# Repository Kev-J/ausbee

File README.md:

Overview
============

Architecture Using STM32 By Eirbot ENSEIRB-MATMECA.
This tool is provided for building automatically a complete STM32F project.

Licence
=============

See LICENCE file.

Usage
=============

- git clone the repository or download the snapshot of the last version.
- If you choose the git clone method, it is recommended to use a tagged version (git checkout vX.X).
- Configure your board (type "make help" for further informations).
- write your source code in Project/src (headers and source files).
- run "make"
- run "make program" for downloading your code into your device.

For further informations, please visit our wiki : https://github.com/Kev-J/ausbee/wiki

Features
=============

- FreeRTOS
- ST Std_Periph_Driver
- libausbee
- stm32flash

Dependencies
=============
* gperf
* flex
* bison
* libncurses-dev (for menuconfig)
* wget
* unzip
* tar
* stm32flash

Please note that this project is using many third party programs. Please ensure
that your setup have all the requirements before using them. For instance,
have a look to the [GCC arm embedded README](https://launchpadlibrarian.net/209775724/readme.txt)
and check that you have all the dependencies installed on your machine before
trying to compile anything.

Authors of the project
=============

Please see AUTHORS

Bugs, patch, requests
=============

https://github.com/Kev-J/ausbee
or
<ausbee@googlegroups.com>

Maintainer : Kevin JOLY <joly.kevin25@gmail.com>

Related to this project
=============

libausbee
-------------
https://github.com/Kev-J/libausbee

ausbee-hardware
-------------
https://github.com/Kev-J/ausbee-hardware

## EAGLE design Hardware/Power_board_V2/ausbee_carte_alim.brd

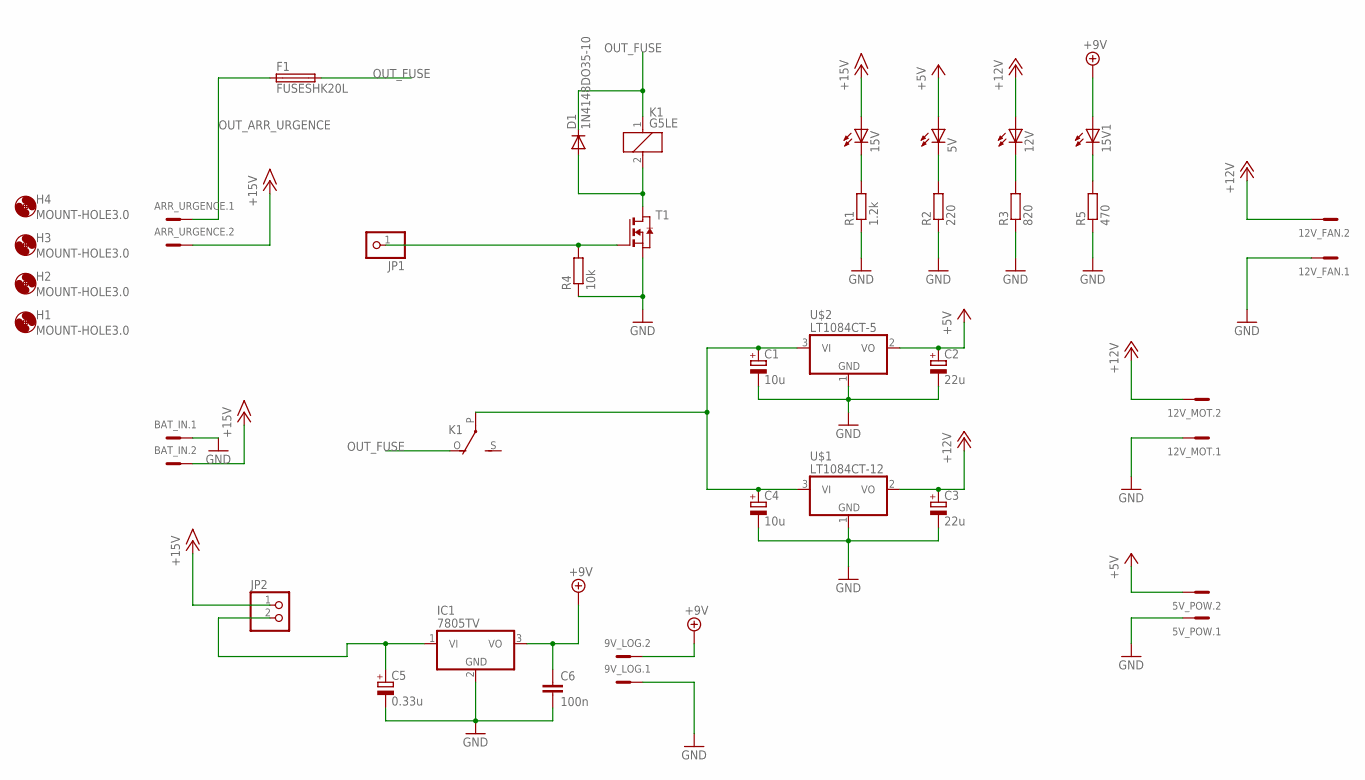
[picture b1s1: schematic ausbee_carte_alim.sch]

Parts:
5V, 12V, 15V, 15V1: LED3MM
5V_POW, 9V_LOG, 12V_FAN, 12V_MOT: MCV2
ARR_URGENCE: MCV2
BAT_IN: MCV2
C1, C4: 10u; E5-8,5
C2, C3: 22u; CT7343
C5: 0.33u; E2,5-5
C6: 100n; C0805
D1: 1N4148DO35-10; DO35-10
F1: FUSESHK20L; SHK20L
H1, H2, H3, H4: MOUNT-HOLE3.0; 3,0
IC1: 7805TV; TO220V
JP1: PINHD-1X1; 1X01
JP2: PINHD-1X2; 1X02
K1: G5LE
R1: 1.2k; 0309V
R2: 220; 0309V
R3: 820; 0309V
R4: 10k; 0309V
R5: 470; 0309V
T1: NMOSSOT23; SOT-23
U$1: LT1084CT-12; TO220V
U$2: LT1084CT-5; TO220V

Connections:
+5V: 5V.A, 5V_POW.2, C2.+, U$2.2 (VO)
+9V: 9V_LOG.2, 15V1.A, C6.1, IC1.3 (VO)
+12V: 12V.A, 12V_FAN.2, 12V_MOT.2, C3.+, U$1.2 (VO)
+15V: 15V.A, ARR_URGENCE.2, BAT_IN.2, JP2.1
GND: 5V_POW.1, 9V_LOG.1, 12V_FAN.1, 12V_MOT.1, BAT_IN.1, C1.-, C2.-, C3.-, C4.-, C5.-, C6.2, IC1.2 (GND), R1.1, R2.1, R3.1, R4.1, R5.1, T1.2 (S), U$1.1 (GND), U$2.1 (GND)
unnamed: 12V.K (C), R3.2
unnamed: 5V.K (C), R2.2
unnamed: 15V.K (C), R1.2
unnamed: C1.+, C4.+, K1.P, U$1.3 (VI), U$2.3 (VI)
unnamed: D1.A, K1.2, T1.1 (D)
unnamed: JP1.1, R4.2, T1.3 (G)
unnamed: C5.+, IC1.1 (VI), JP2.2
unnamed: 15V1.K (C), R5.2
OUT_ARR_URGENCE: ARR_URGENCE.1, F1.1A (1)
OUT_FUSE: D1.C, F1.2A (2), K1.1, K1.O

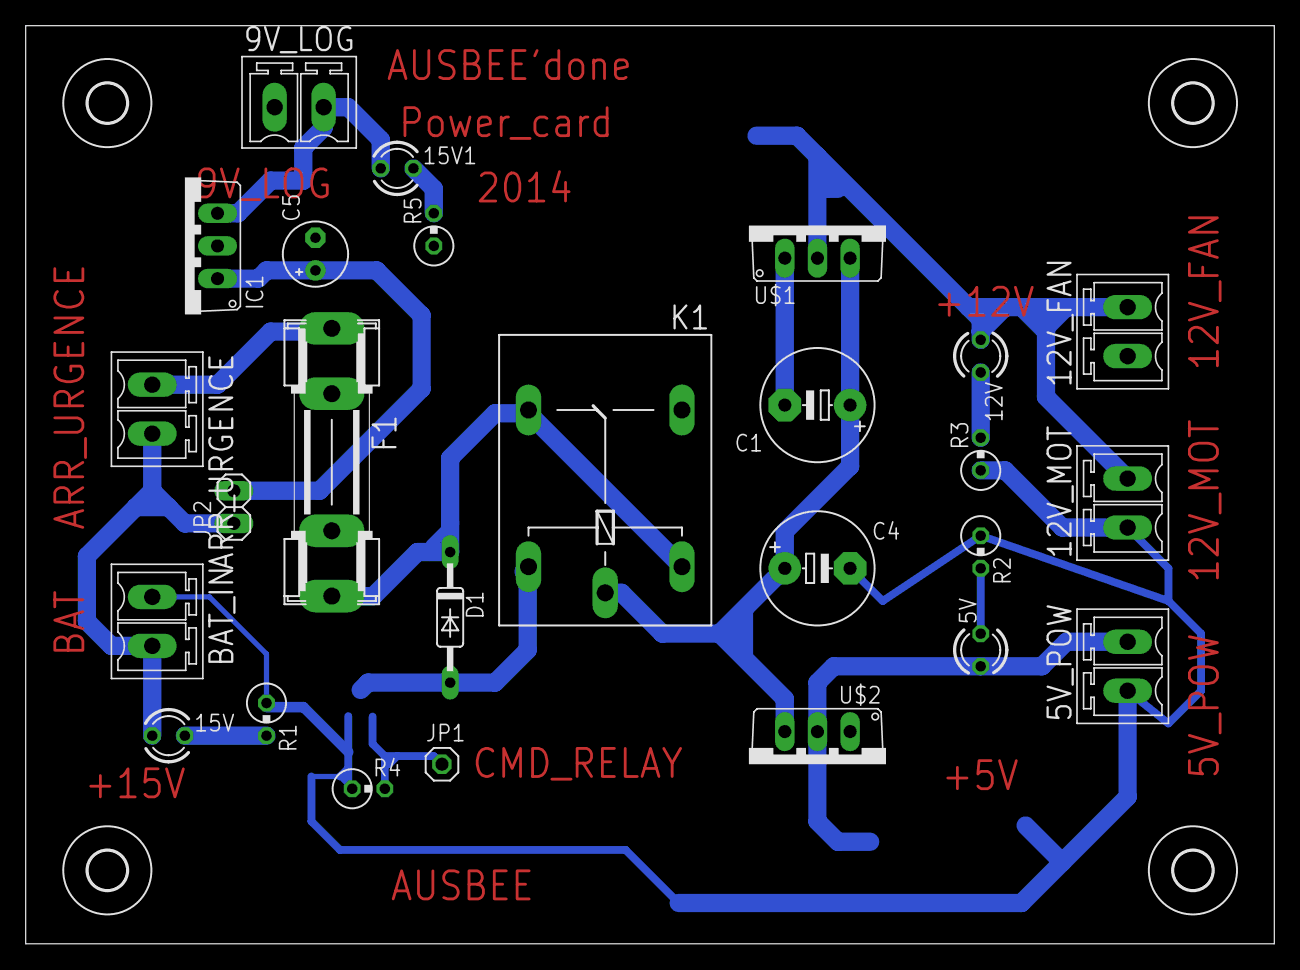
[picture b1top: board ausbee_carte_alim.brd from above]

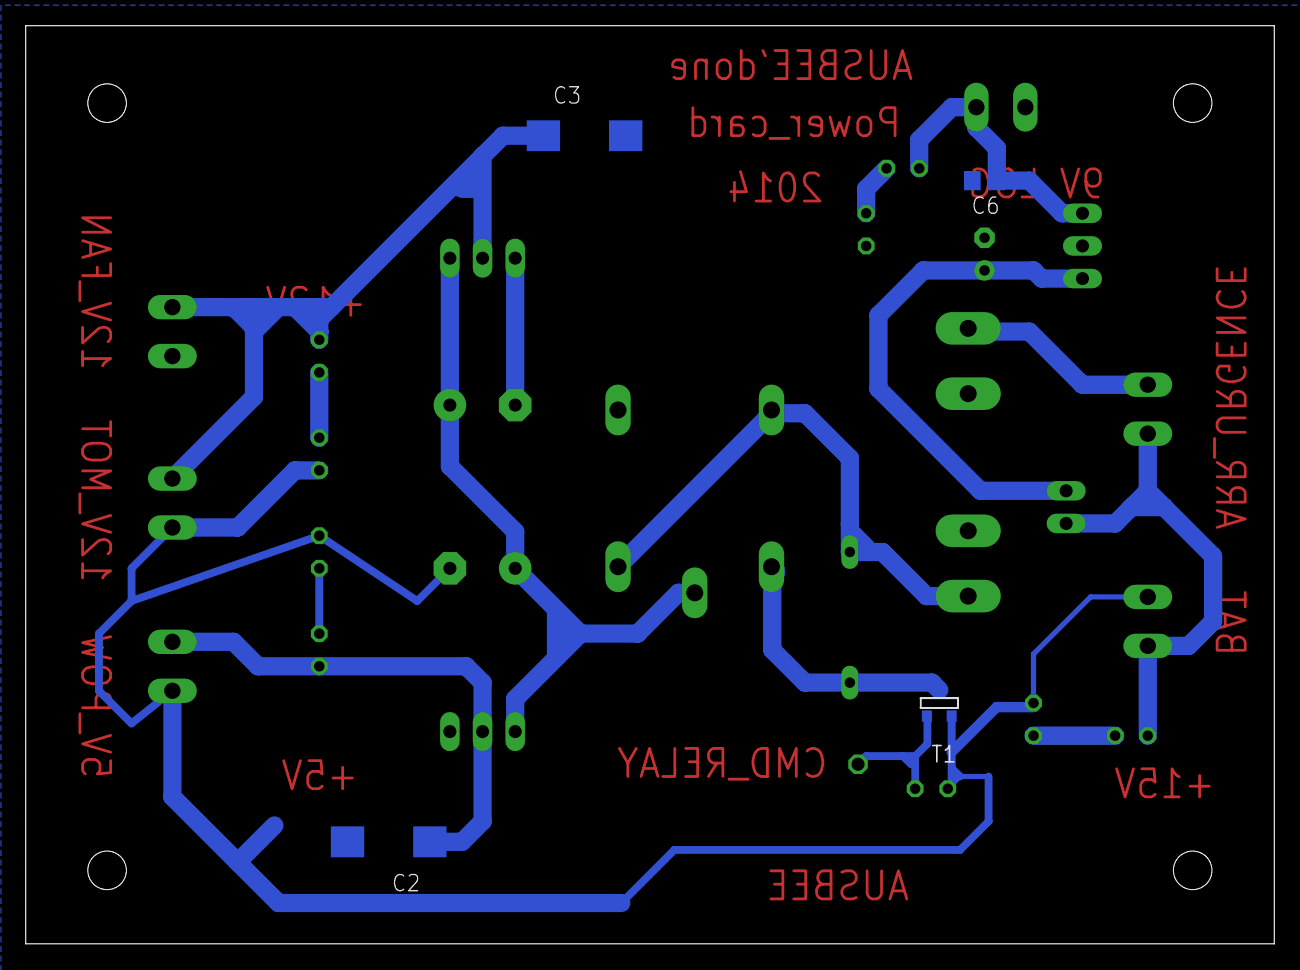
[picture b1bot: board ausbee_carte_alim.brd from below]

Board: 2 copper layers, 97.1 x 71.4 mm, 34 parts (4 on the bottom side), 15 nets.

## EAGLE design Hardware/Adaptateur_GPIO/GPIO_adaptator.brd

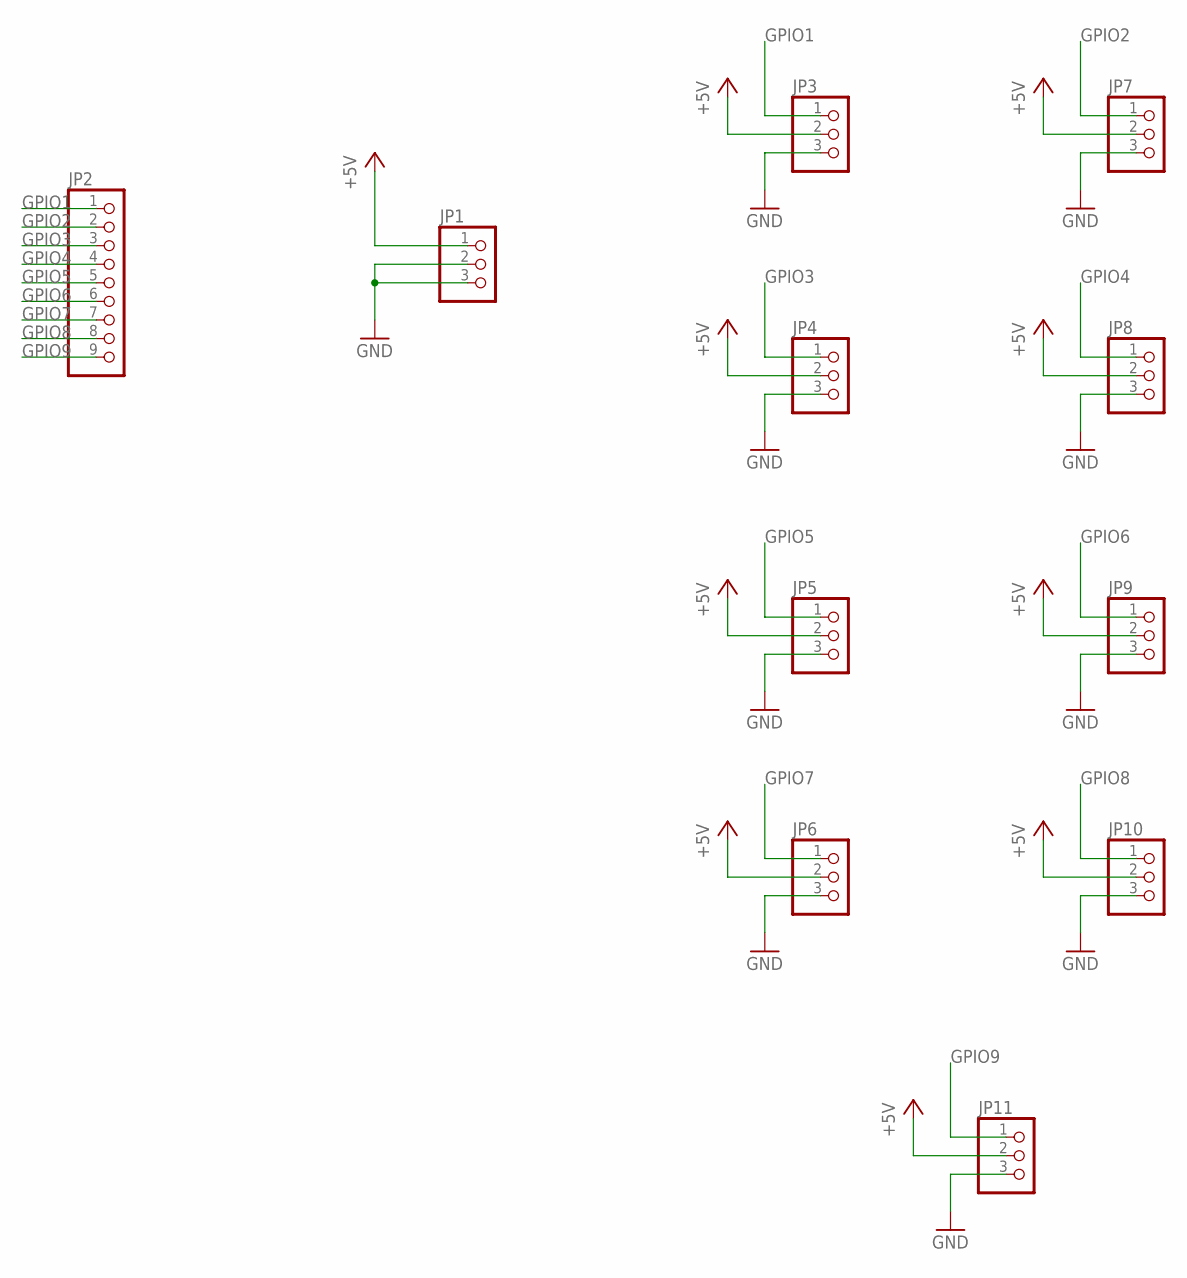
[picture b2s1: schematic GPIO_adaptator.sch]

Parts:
JP1, JP3, JP4, JP5, JP6, JP7, JP8, JP9, JP10, JP11: PINHD-1X3; 1X03
JP2: PINHD-1X9; 1X09

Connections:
+5V: JP1.1, JP3.2, JP4.2, JP5.2, JP6.2, JP7.2, JP8.2, JP9.2, JP10.2, JP11.2
GND: JP1.2, JP1.3, JP3.3, JP4.3, JP5.3, JP6.3, JP7.3, JP8.3, JP9.3, JP10.3, JP11.3
GPIO1: JP2.1, JP3.1
GPIO2: JP2.2, JP7.1
GPIO3: JP2.3, JP4.1
GPIO4: JP2.4, JP8.1
GPIO5: JP2.5, JP5.1
GPIO6: JP2.6, JP9.1
GPIO7: JP2.7, JP6.1
GPIO8: JP2.8, JP10.1
GPIO9: JP2.9, JP11.1

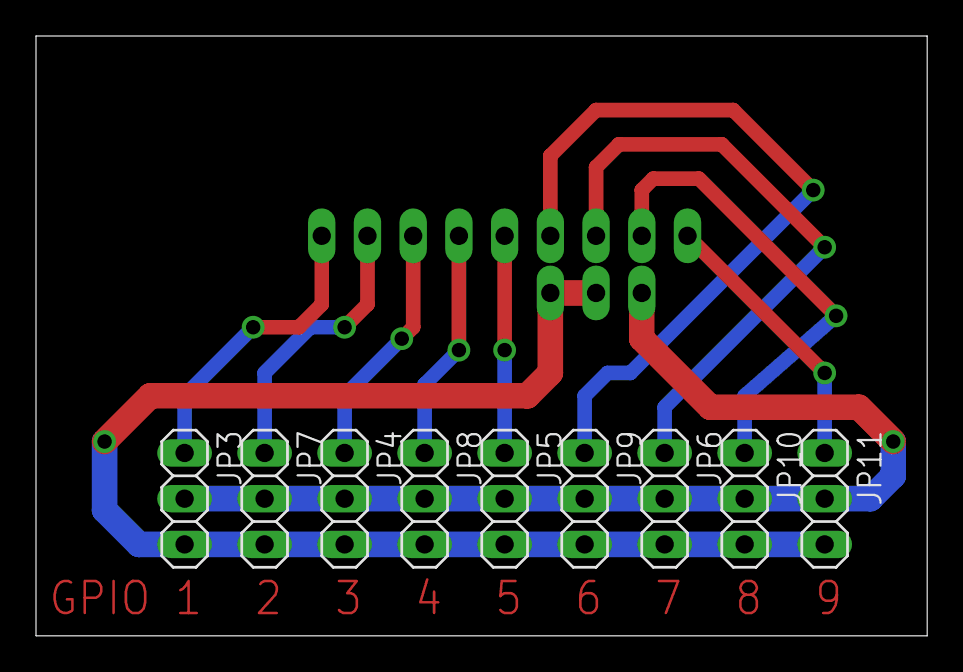
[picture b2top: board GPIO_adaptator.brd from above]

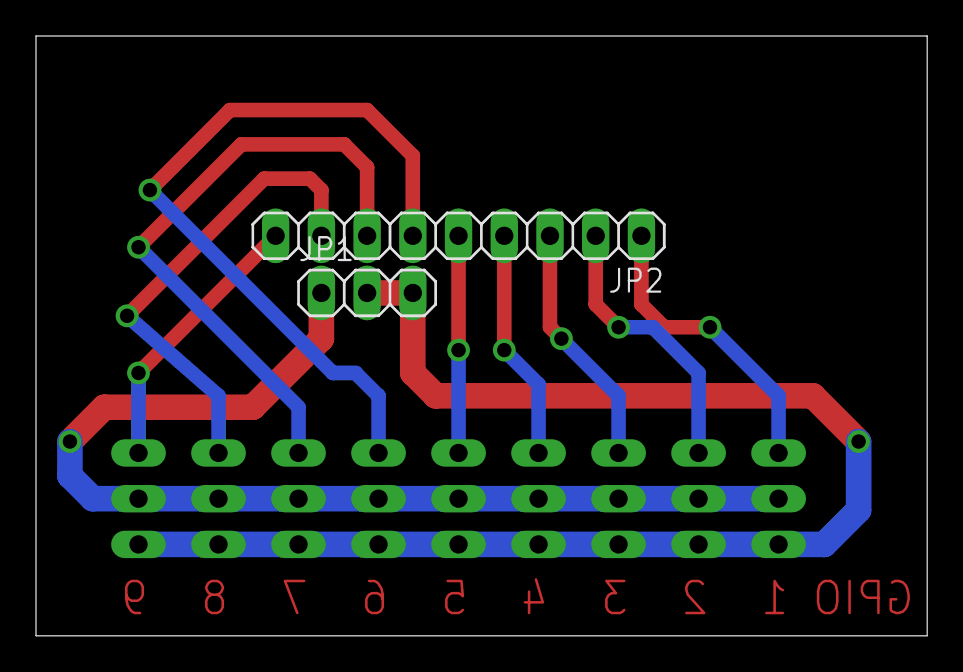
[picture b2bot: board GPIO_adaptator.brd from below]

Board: 2 copper layers, 49.5 x 33.3 mm, 11 parts (2 on the bottom side), 11 nets.

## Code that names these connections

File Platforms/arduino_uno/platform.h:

#ifndef PLATFORM_H
#define PLATFORM_H

#include <stdint.h>

#define GPIO0   (1 << 0)
#define GPIO1   (1 << 1)
#define GPIO2   (1 << 2)
#define GPIO3   (1 << 3)
#define GPIO4   (1 << 4)
#define GPIO5   (1 << 5)
#define GPIO6   (1 << 6)
#define GPIO7   (1 << 7)
#define GPIO8   (1 << 8)
#define GPIO9   (1 << 9)
#define GPIO10  (1 << 10)
#define GPIO11  (1 << 11)
#define GPIO12  (1 << 12)
#define GPIO13  (1 << 13)

typedef enum
{
  PLATFORM_GPIO_INPUT,
  PLATFORM_GPIO_OUTPUT,
} platform_gpio_dir_t;

void platform_init(void);

void platform_gpio_init(uint16_t gpio, platform_gpio_dir_t direction);
void platform_gpio_set(uint16_t gpio);
void platform_gpio_clear(uint16_t gpio);

#endif// PLATFORM_H

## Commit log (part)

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2013-10-22 [HARDWARE] routing
2013-10-25 [HARDWARE][SERVO_MODULE] Schematic
2013-10-25 [HARDWARE][SWD_adapter]schema+routage
2013-10-25 [HARDWARE][SWD_Adapter]routage a verifier
2013-10-26 [HARDWARE][SWD_Adapter]Ajout des plans de masse
2013-10-27 [HARDWARE][SERVO_MODULE] Board legend
2013-10-27 [HARDWARE][SERVO_MODULE] Add board .brd
2013-11-04 [HARDWARE][SWD_Adapter]Routage: capa de decouplage plus proches des pins
2013-11-05 [HARDWARE][SERVO_MODULE] Add GND plane on board
2013-11-05 [HARDWARE][SWD_Adapter]correction de routage
2013-11-07 Remove build tool CMAKE files for kconfig-frontends
2013-11-08 [HARDWARE][SERVO_MODULE] Typon files correction
2013-11-08 [HARDWARE][SERVO_MODULE] Final schematic. Change some footprint and line width
2013-11-15 [SOFTWARE] PID creation
2013-11-22 [SOFTWARE] Add error message when no configuration file has been found
2013-11-22 [SOFTWARE] Define a new structure of building project
2013-11-22 [SOFTWARE] Rearrange all directory architecture
2013-11-22 [Software]Remove files with ~
2013-11-22 [SOFTWARE] Add StdPeriph drivers for STM32F4xx and remove lib directory
2013-11-23 [SOFTWARE] Remove a swp file
2013-11-23 start generic class CAN
2013-11-23 [SOFTWARE] Change the way to select the device
2013-11-23 slight modif on can.h can.c
2013-11-23 [SOFTWARE][LIBAUSBEE] Reorganise directories and remove autotools
2013-11-24 constructor of class CAN
2013-11-24 [SOFTWARE][LIBAUSBEE] Add libausbee's makefile
2013-11-24 [SOFTWARE] Enable the user to call make clean or make dirclean when no config has been found
2013-11-24 [SOFTWARE] Add stm32flash support
2013-11-24 [SOFTWARE][LIBAUSBEE] Rename examples in tools and make ausbee-lidar-viewer compiling with CMake
2013-11-24 [SOFTWARE][DOC] Init files
2013-11-24 [SOFTWARE] Add make help rule
2013-11-24 [SOFTWARE] fix config.mk mistake about .config loading
2013-11-24 [SOFTWARE] startup script test
2013-11-26 [SOFTWARE] Enable g++ optimisations
2013-11-26 [SOFTWARE] Add some infos
2013-11-26 [SOFTWARE] Change obj dependancies mechanism and make use of FreeRTOS being optionnal
2013-11-26 [SOFTWARE] Keep comments when preprocessing linker script
2013-11-26 [SOFTWARE] Move FreeRTOS to Operating_Systems directory
2013-11-26 [SOFTWARE] TODO
2013-11-26 [SOFTWARE] Make Cortex-M4 compiling
2013-11-27 [SOFTWARE] Add CM3 syscalls
2013-11-29 [SOFTWARE][DOC] Rename the stdperiph correct name
2013-11-29 [SOFTWARE] Add platform directory
2013-11-30 [SOFTWARE] Change makefile order
2013-11-30 [SOFTWARE] Add stm32 header to syscalls
2013-11-30 [SOFTWARE] Reorganise Kconfig and set debug support
2013-11-30 [SOFTWARE] Add led support in libausbee
2013-11-30 [SOFTWARE] Remove main_board_v0 config
2013-11-30 [SOFTWARE] Make the assert system dependant to DEBUG macro
2013-11-30 [SOFTWARE] Add crystal oscillator macro
2013-11-30 [SOFTWARE][PLATFORM] Add platform.c for ausbee_main_board_v0.1
2013-11-30 [SOFTWARE] Fix header name
2013-12-03 [SOFTWARE][LIBAUSBEE] Remove led module
2013-12-03 [SOFTWARE] Improve clean goals
2013-12-03 [SOFTWARE][SYSTEM-CM4] Remove a bracket
2013-12-03 [SOFTWARE][SYSTEM-CM4] Add optimisation
2013-12-03 [SOFTWARE] TODO list
2013-12-03 [SOFTWARE][PLATFORMS] Fix clean goals
2013-12-03 [SOFTWARE][DOC] Add STM32F4xx_StdPeriph doxyfile
2013-12-03 [SOFTWARE] Enable FPU
2013-12-07 [SOFTWARE][OS] Set NONE the first choice
2013-12-07 [SOFTWARE] Fix syscalls
2013-12-08 slight modification on platform for CAN
2013-12-08 [SOFTWARE] Make the L298 available in Kconfig
2013-12-08 [SOFTWARE] update TODO
2013-12-08 [SOFTWARE] Add CAN init function to the header file
2013-12-08 [Software]add servo module platform
2013-12-08 [SOFTWARE] Add init motor 2 and modify init motor1
2013-12-08 [SOFTWARE] Enable the use of FPU for F4
2013-12-08 [SOFTWARE] Add library servo in libausbee
2013-12-12 [SOFTWARE] Change STM32F4xx stdperiph name
2013-12-14 [SOFTWARE]Update kconfig for stm32f10x libraries
2013-12-20 add misc in Kconfig
2013-12-20 [SOFTWARE] Modify USART config on platform.c
2013-12-20 [SOFTWARE]remove .o files
2013-12-20 [SOFTWARE]Update servo module platform
2013-12-27 schematic power card
2013-12-31 modification on power board: add relay and fuse
2014-01-09 add MOS instead of bipolar and change fuse footprint
2014-01-10 [SOFTWARE]Add example folder + update servo module platform
2014-01-10 [SOFTWARE]Remove main.h in Robot Code Example
2014-01-10 [SOFTWARE] Add Doxyfile for documentation
2014-01-12 [SOFTWARE] Corrected spelling mistakes + removed unwanted tabs
2014-01-13 [SOFTWARE][QUADRAMP] Drawing generated speed and acceleration
2014-01-27 add GPIO in platform
2014-01-27 Power board V2, adaptator GPIO
2014-01-28 modif on .mk, platform, and servo for portability
2014-01-28 [SOFTWARE][LIBAUSBEE] Remove asserv and add Control engineering functions
2014-01-28 [SOFTWARE][LIBAUSBEE] Doc
2014-01-28 add pwm init in platform
2014-01-29 [SOFTWARE][LIBAUSBEE] Add lidar support and make it compliant with the lidar_viewer tool
2014-02-06 [SOFTWARE]Add SPI sources in configuration files
2014-02-07 [SOFTWARE]Add programmer select in menuconfig
2014-02-08 [SOFTWARE]Update f4discovery platform + f4discovery example code
2014-02-08 [SOFTWARE]Update F4Discovery platform and example
2014-02-28 [SOFTWARE]Add AX12 in libausbee
2014-03-15 remove include of platform.h in ax12
2014-03-16 removed can from libausbee and slight modif in l298 driver
2014-03-21 add other usart in platform init and remove lidar.h include from lidar.h
2014-04-05 add define in platform.h
2014-04-12 [TEXT] Adding a .gitignore in Software
2014-04-13 Adding Command line interface (Beta)
2014-04-13 Tool to plot encoder value with PID
2014-04-13 [SOFT] Adding encoder to libausbee
2014-04-13 [SOFT] Adding a first control system manager
2014-04-13 [SOFT][LIBAUSBEE] Update encoder module
2014-04-16 [SOFT] Emptying project's sources to create a separate repo for it
2014-04-19 [SOFT] Fixed lidar_viewer compilation
2014-04-26 [SOFTWARE] Subdirectories now possible in projects
2014-04-27 [SOFT] csm is no longer dependent on the type of controller used (such as a pid)
2014-04-27 [SOFT] Creating a debug_printf macro for debugging purpose
2014-04-27 [SOFT] Fixed int32_t in printf warning
2014-04-28 [SOFT] Starting a quest against warnings.
2014-04-28 [SOFT] Encoder1 now working!
2014-04-28 [SOFT] Removed binary file + ignoring them
2014-05-01 [SOFT] Adding a tool to plot pid value
2014-05-01 [SOFT] Generic ploting tool
2014-05-01 Uniformisation of platform functions
2014-05-02 [SOFT] pid: new function to change reference
2014-05-02 [SOFT] Ploting pid values for both motors
2014-05-03 [SOFT] Plotting robot distance
2014-05-09 [SOFT] Clock init in separate function
2014-05-09 [SOFT] plotting tool: can print floats
2014-05-10 [SOFT] plotting tool: printing any size of data sample
2014-05-10 [SOFT] plotting tool: highlighting current robot position
2014-05-11 [SOFT] control system now gets the reference as param
    A new function is used to get the measure.
    Controllers now take error as params rather than reference.
2014-05-14 [SOFT] intergers replaced by floats in control system
2014-05-14 [SOFT] pid: function naming standardization + better interface
2014-05-18 [SOFT] cs: adding a diff filter on measure
2014-05-18 [SOFT][DOC] Adding some missing doc
2014-05-18 [SOFT] plotting tool: fixed y axe data range
2014-05-24 [SOFT] movement_generation: removed, replaced by quadramp filter
2014-05-24 remove other debug printf in platform
2014-05-24 [SOFT] diff: fixed doc
2014-05-25 [SOFT] pid: coeffs are floats
2014-05-25 [SOFT] plotting tool: better parameters
2014-05-26 [SOFT] pid: adding setter and getters for pid parameters
2014-09-23 Remove Libraries dir
2014-09-23 Remove documentation directory
2014-09-23 Make the ausbee_main_board platform compliant with last commit
2015-05-03 Removing misplaced file
2015-05-08 Ausbee platform: now supporting encoders with quadrature
2015-05-08 Using latest libausbee-1.0 that supports encoders with quadrature
2015-05-21 add multiproject support for menuconfig
2015-05-21 add multiproject compilation. Need to put object files in a project subdirectory
2015-05-21 generate project object file in Output/Project directory
2015-05-21 generate ausbee object file in project output directory
2015-05-22 generate platform object files in projet output directory
2015-05-22 add the ability to use system path for toolchain binaries
2015-05-26 Fix stm32f10x_stdperiph path
2015-05-26 Add a changelog
2015-05-26 Add include dir to .gitignore rules
2015-05-26 Change the toolchain extracted path into build subdirectory
2015-05-26 Remove old ld file from .gitignore
2015-05-27 new indentation of Kconfig
2015-06-09 Add custom platforms Kconfig to general makemenuconfig
2015-06-10 fix comments
2015-06-11 move custom platforms config from Makefile to menconfig
2015-06-11 Add subdirectories of Project in .gitignore
2015-06-11 Add GPLv3
2015-06-12 fix displayed size
2015-06-12 add program rule for avrdude
2015-06-14 add ability to get libausbee from git
2015-06-14 too much cleaning !
2015-06-17 path for include inside Kconfig
2015-06-22 handle custom platform and set correct ram and flash values for official platforms
2015-06-24 Add AUTHORS file and improve README.md
2015-06-24 Add some extra informations under Dependencies section in README.md
2015-06-24 Handle FreeRTOS config in Kconfig
2015-07-01 add xmega128a1 support
2015-07-01 force usb if isp mkII is selected
2015-07-02 add .config as dependancy to all object & link generation
2015-07-02 generate dependancy files for packages
2015-07-02 generate dependancy files for system-cmX
2015-07-02 fix generated path
2015-07-03 fix dependancy generation for make clean rule
2015-07-04 fix Kconfig for programming baudrate & interface
2015-07-04 avr port need a freeRTOS version >=8.0.0
2015-07-08 Fix file dependancies in makefiles
2015-07-17 remove cast for MAX_PRIORITIES. The cast is useless(?) and break build with FreeRTOS v>=8.0.0
2015-07-19 Don't break FreeRTOS v7 build
2015-07-25 Add some directions to ensure that the correct clock of the MCU is selected
2015-10-19 Download all package before starting to build
2015-10-19 use global operating system include list variable
2015-10-19 fix makefile script for host target
2015-10-20 Rewrite code for simulation build. Better integration into ausbee
2015-10-21 Fix multiproject bug ; Add script for creating projects
2015-10-21 fix colored echo
2015-10-21 remove pkg-generic-old
2015-10-21 Add chip-info and debugging
2015-10-25 fix output file name
2015-10-25 add new define for TARGET/SIM differentiation
2016-03-10 add gnu99 when compiling in sim mode (for old gcc)
2016-03-23 add eventÃ_groups freertos modules
2016-05-20 [PLATFORMS] Add stm32f7discovery platform
2016-05-20 [PLATFORMS] Fix stm32f4discovery built_print call
2016-05-23 [PLATFORMS] Update stm32f7discovery platform
2016-05-23 [SYSTEM][CM7] Fix typo
2016-05-24 [TOOLCHAIN] Switch to gcc-arm-embedded 5-2016-q1 for default configuration
2016-05-24 Ignore downloads directory
2016-05-24 [PACKAGES] Remove debug print
2016-05-24 Fix CM0+ macro in config.mk
2016-05-31 [PACKAGES] Add stm32_usb_device_library package
2016-05-31 [SYSTEM][CM0Plus] Add end of stack symbols in linker script
2016-06-01 [PLATFORM][STM32F7DISCOVERY] Add menu
2016-06-01 Print size after link
2016-06-09 [PLATFORM][STM32F7DISCOVERY] Add storage drivers
2016-06-09 Add semihosting support for CM7 and OpenOCD
2016-06-26 Add a way to auto-discover package source files. Useful if you are working on a separated branch with a different source file list
2017-06-13 fix build with gperf 3.1
2017-06-13 Gperf 3.1 fix broke build for Gperf 3.0.x
2017-06-15 create output directory before generating link
2017-06-15 fix find on mac
2017-06-15 add gnu99 as default
2017-06-18 Add freeRTOS POSIX port in freertos makefile
2017-10-25 Add new freeRTOS linux port
2018-04-13 add Kconfig option for xmega
2018-04-13 fix avr-ld usage for step board
2018-09-30 Add exit command to openocd command line
2018-11-10 various fixes written during the 2018 robotic cup
2018-11-10 autogenerate git header
2018-12-08 missing file
2019-04-19 Add system for M0 et L4
